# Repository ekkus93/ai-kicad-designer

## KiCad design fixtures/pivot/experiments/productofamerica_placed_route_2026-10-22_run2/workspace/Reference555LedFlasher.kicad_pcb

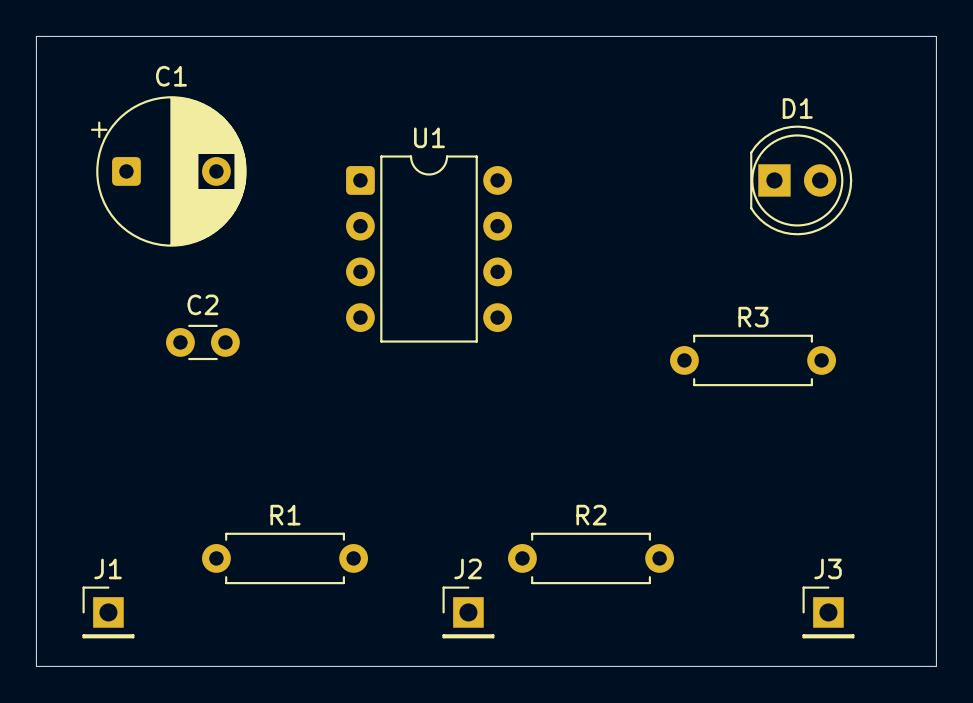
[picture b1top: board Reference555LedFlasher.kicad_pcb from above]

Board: 2 copper layers, 50.0 x 35.0 mm, 10 parts (0 on the bottom side), 7 nets, no tracks yet.

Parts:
C1: 10u; CP_Radial_D8.0mm_P5.00mm
C2: 10n; C_Disc_D3.0mm_W1.6mm_P2.50mm
D1: WP7113ID; LED_D5.0mm
J1: Supply; PinHeader_1x01_P2.54mm_Vertical
J2: Pulse output; PinHeader_1x01_P2.54mm_Vertical
J3: Return; PinHeader_1x01_P2.54mm_Vertical
R1: 10k; R_Axial_DIN0207_L6.3mm_D2.5mm_P7.62mm_Horizontal
R2: 47k; R_Axial_DIN0207_L6.3mm_D2.5mm_P7.62mm_Horizontal
R3: 1k; R_Axial_DIN0207_L6.3mm_D2.5mm_P7.62mm_Horizontal
U1: NE555D; DIP-8_W7.62mm

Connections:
/OUT: D1.1, J2.1, U1.3
/REF: C1.2, C2.2, J3.1, U1.1
/VCC: J1.1, R1.1, R3.1, U1.4, U1.8
unnamed: D1.2, R3.2
unnamed: C2.1, U1.5
unnamed: R1.2, R2.1, U1.7
unnamed: C1.1, R2.2, U1.2, U1.6
